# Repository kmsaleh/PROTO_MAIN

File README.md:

# PROTO_MAIN
This is my KICAD project files for the new PCB

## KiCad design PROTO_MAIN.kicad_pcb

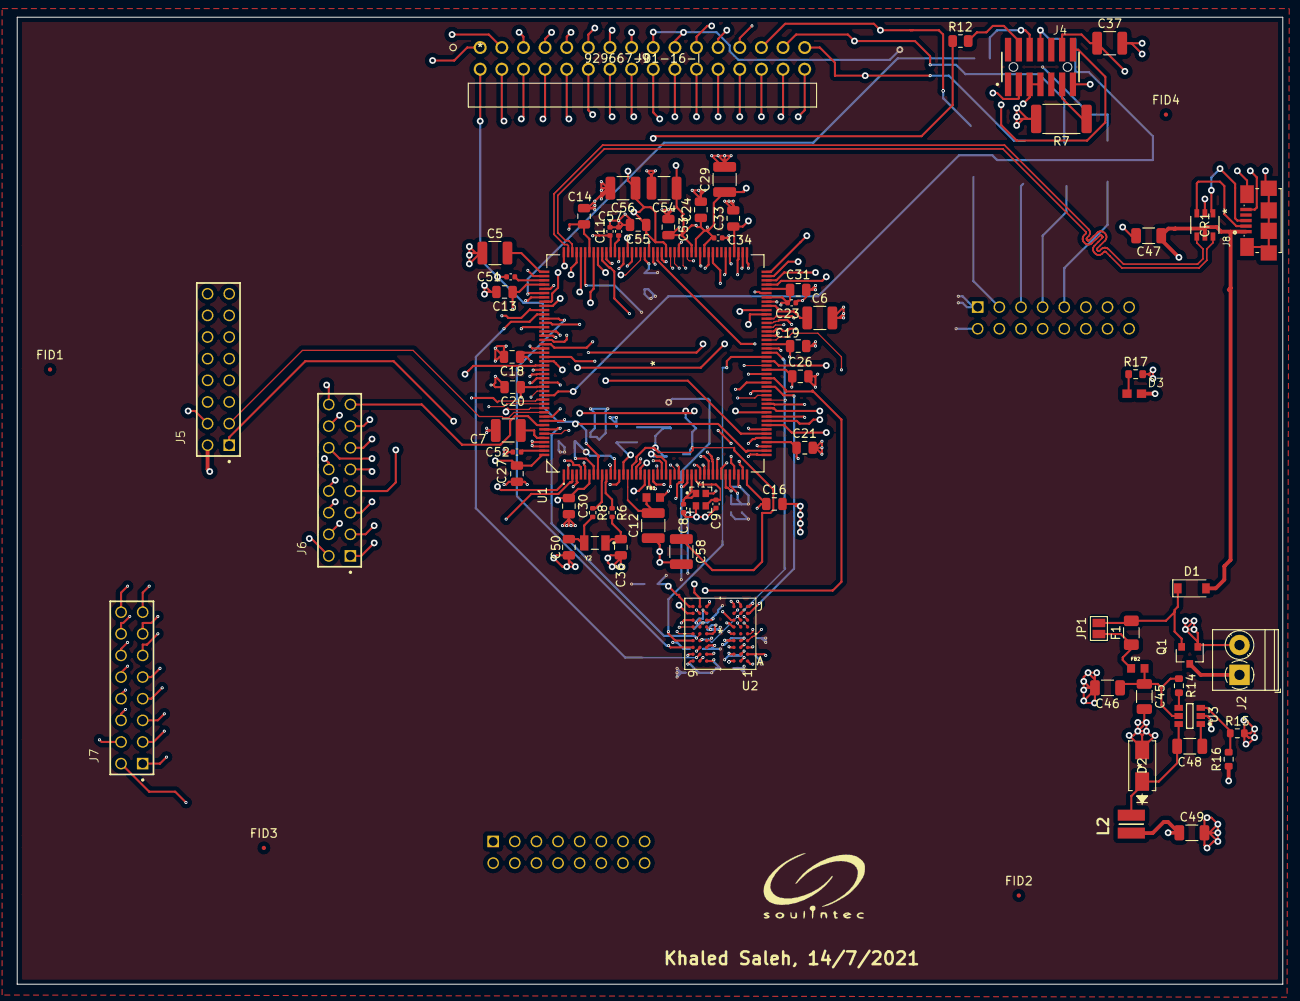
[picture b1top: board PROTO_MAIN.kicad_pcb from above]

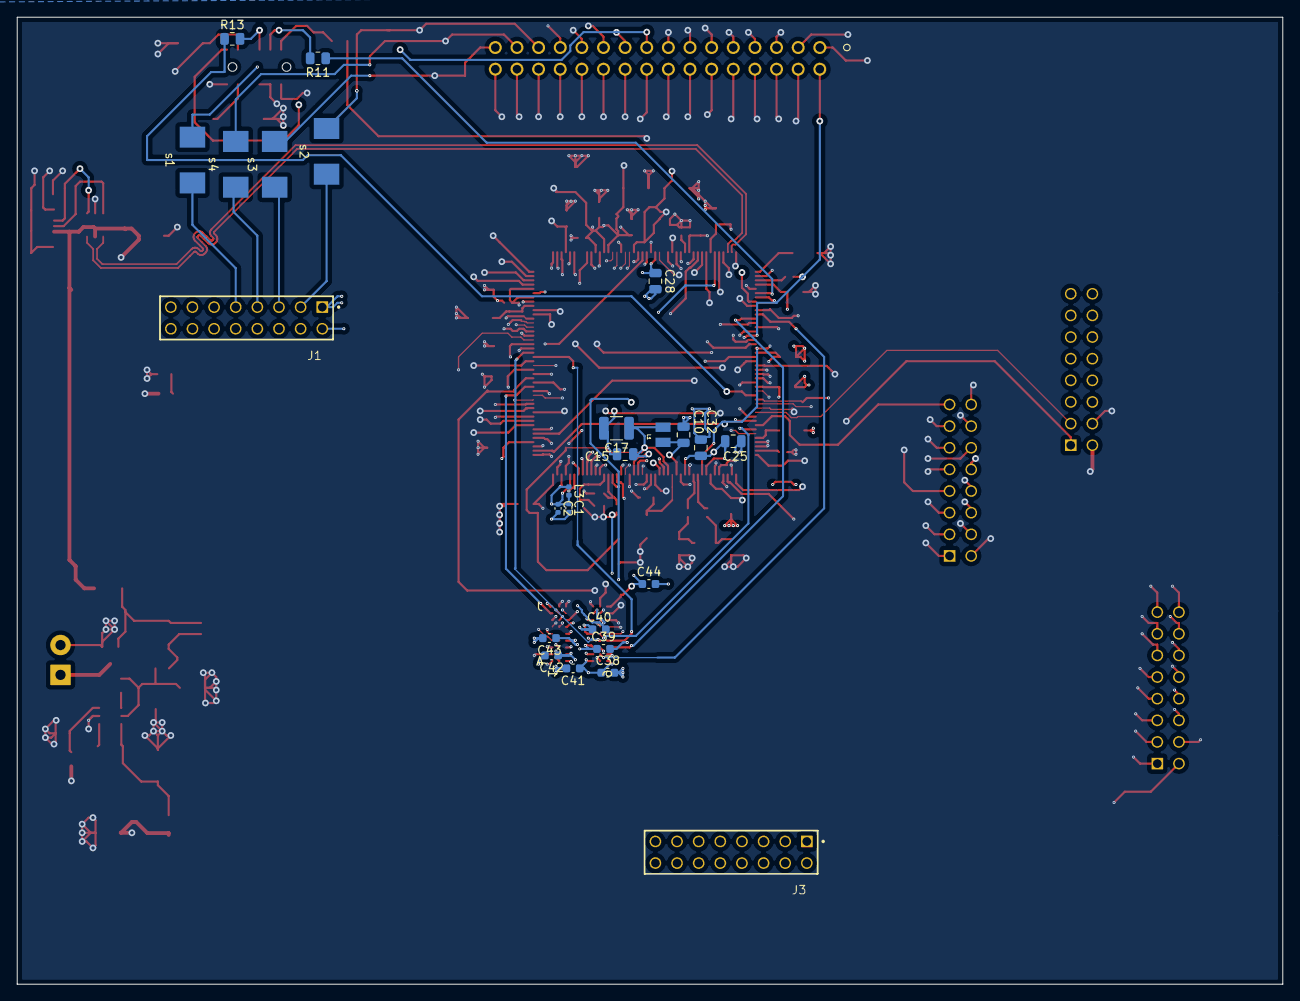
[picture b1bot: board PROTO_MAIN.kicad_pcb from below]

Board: 12 copper layers, 148.6 x 113.5 mm, 98 parts (25 on the bottom side), 144 nets.

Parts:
C1, C11, C57: 1uF; C_0402_1005Metric
C2: 10nF; C_0402_1005Metric
C5, C6, C7: 4.7uF; C_1210_3225Metric
C8, C9: 5.6pF; C_0402_1005Metric
C10: 220pF; C_0805_2012Metric
C12, C17, C58: 10uF; C_1210_3225Metric
C13, C14, C15, C16, C18, C19, C20, C21, C25, C26, C27, C28, C30, C31, C32, C33: 100uF; C_0805_2012Metric
C23, C34, C51, C52: 4.7uF; C_0402_1005Metric
C24, C53, C55: 100nF; C_0805_2012Metric
C29, C54, C56: 2.2uF; C_1210_3225Metric
C36, C50: 1.5pF; C_0805_2012Metric
C37: 0.1uF; C_1210_3225Metric
C38, C39, C40, C41, C42, C43, C44: 100nF; C_0603_1608Metric
C45: 10U; C_1206_3216Metric
C46: 10uF 25V; C_1206_3216Metric
C47: 100nF; C_1206_3216Metric
C48: 22nF; C_1206_3216Metric
C49: 22uF 6.3V; C_1206_3216Metric
CR1: USBLC6-4SC6
D1: B5819W; D_SOD-123
D2: B230A-13-F
D3: LED_Red; 0603
F1: 0685H9150-01; Fuse_1206_3216Metric
FB1, FB2: FBMJ1608HM180NTR; BEADC1608X100N
FID1, FID2, FID3, FID4: Fiducial; Fiducial_0.5mm_Mask1.5mm
J1, J3, J5, J6, J7: ZW-08-09-F-D-440-110; SAMTEC_ZW-08-09-F-D-440-110
J2: Screw_Terminal_01x02; TerminalBlock_Phoenix_PT-1,5-2-3.5-H_1x02_P3.50mm_Horizontal
J4: FTSH-107-01-L-DV-K-A; SAMTEC_FTSH-107-01-L-DV-K-A
J8: 10118192-0001LF; AMPHENOL_10118192-0001LF
J9: 929667-01-16-I
JP1: Jumper_NO_Small; SolderJumper-2_P1.3mm_Open_Pad1.0x1.5mm
L1: LQM2MPN2R2MG0L; INDC2016X100N
L2: 4.7uH; INDC3030X200N
L3: 39n; L_0402_1005Metric
Q1: AO3401A; SOT-23
R6, R8: 0R; R_0402_1005Metric
R7: 100R; R_2512_6332Metric
R11, R12, R13: 22R; R_0805_2012Metric
R14: 100K; R_0603_1608Metric
R15: 16.2K; R_0603_1608Metric
R16: 49.9k; R_0603_1608Metric
R17: 1k; R_0603_1608Metric
U1: STM32H747IIT6
U2: IS42S16160J-7BLI
U3: MP2359DT-LF-Z; Richtek_USA_Inc-RT8259GE-0
Y1: NX2016SA-25M-EXS00A-CS08742; OSCCC200X160X50N
Y2: NX3215SA-32.768K-STD-MUA-8; XTAL_NX3215SA-32.768K-STD-MUA-14
s1, s2, s3, s4: S1911-46R; S1621-46R

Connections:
+3V3: C1.1, C2.1, C11.1, C13.1, C14.1, C15.1, C16.1, C17.1, C18.1, C19.1, C20.1, C21.1, C23.1, C24.1, C25.1, C26.1, C27.1, C28.1, C29.1, C30.1, C31.1, C32.1, C33.1, C34.1, C38.1, C39.1, C41.1, C42.1, C43.1, C44.1, C49.1, C53.1, C54.1, C55.1, C56.1, D3.2, FB1.2, J1.02, J4.03, J5.04, L1.2, L2.2, L3.1, L3.2, R16.1, U1.7, U1.8, U1.13, U1.25, U1.39, U1.40, U1.44, U1.48, U1.65, U1.71, U1.82, U1.84, U1.92, U1.99, U1.101, U1.102, U1.108, U1.113, U1.121, U1.126, U1.136, U1.152, U1.160, U1.176, U2.A7, U2.A9, U2.B3, U2.C7, U2.D3, U2.J9
+5V: C47.1, CR1.5, D1.2, J5.02, J8.1
+12V: J2.1, Q1.3
/103: J9.32, U1.103
/104: J9.31, U1.104
/106: J9.30, U1.106
/107: J9.29, U1.107
/LCD_B0: J6.01, U1.158
/LCD_B1: J6.03, U1.156
/LCD_B2: J6.05, U1.154
/LCD_B3: J6.07, U1.155
/LCD_B4: J6.09, U1.129
/LCD_B5: J6.11, U1.46
/LCD_B6: J6.13, U1.168
/LCD_B7: J6.15, U1.169
/LCD_CLK: J6.14, U1.117
/LCD_DE: J6.08, U1.30
/LCD_DISP: J6.10, U1.1
/LCD_G0: J7.02, U1.56
/LCD_G1: J7.04, U1.5
/LCD_G2: J7.06, U1.51
/LCD_G3: J7.08, U1.125
/LCD_G4: J7.10, U1.78
/LCD_G5: J7.12, U1.79
/LCD_G6: J7.14, U1.123
/LCD_G7: J7.16, U1.118
/LCD_HSYNC: J6.02, U1.122
/LCD_INT: J6.06, U1.35
/LCD_R0: J7.01, U1.157
/LCD_R1: J7.03, U1.43
/LCD_R2: J7.05, U1.42
/LCD_R3: J7.07, U1.55
/LCD_R4: J7.09, U1.50
/LCD_R5: J7.11, U1.128
/LCD_R6: J7.13, U1.127
/LCD_R7: J7.15, U1.116
/LCD_RESET: J6.12, U1.2
/LCD_VSYNC: J6.04, U1.49
/NRST: C37.1, J4.12, U1.33
/PA0: J9.7, U1.41
/PA7: J9.8, U1.52
/PA15: J9.3, U1.139
/PB2: J9.11, U1.57
/PB4: J9.2, U1.163
/PB5: J9.1, U1.164
/PC0: J9.4, U1.34
/PC2_C: J9.5, U1.36
/PC3_C: J9.6, U1.37
/PC4: J9.9, U1.53
/PC5: J9.10, U1.54
/PC12: J9.23, U1.142
/PC13: J9.17, U1.9
/PD3: J9.24, U1.146
/PD4: J9.25, U1.147
/PD6: J9.26, U1.149
/PD7: J9.27, U1.150
/PE5: J9.18, U1.4
/PE7: J9.12, U1.67
/PF6: J9.19, U1.26
/PF7: J9.20, U1.27
/PF8: J9.21, U1.28
/PF9: J9.22, U1.29
/PG9: J9.28, U1.153
/RX: J4.13, U1.141
/SCL: J5.01, U1.165
/SDA: J5.03, U1.166
/SDRAM_A0: U1.18, U2.H7
/SDRAM_A1: U1.19, U2.H8
/SDRAM_A2: U1.20, U2.J8
/SDRAM_A3: U1.21, U2.J7
/SDRAM_A4: U1.22, U2.J3
/SDRAM_A5: U1.23, U2.J2
/SDRAM_A6: U1.59, U2.H3
/SDRAM_A7: U1.60, U2.H2
/SDRAM_A8: U1.61, U2.H1
/SDRAM_A9: U1.62, U2.G3
/SDRAM_A10: U1.63, U2.H9
/SDRAM_A11: U1.66, U2.G2
/SDRAM_A12: U1.110, U2.G1
/SDRAM_BA0: U1.111, U2.G7
/SDRAM_BA1: U1.114, U2.G8
/SDRAM_CLE: U1.94, U2.F3
/SDRAM_CLK: U1.145, U2.F2
/SDRAM_D0: U1.97, U2.A8
/SDRAM_D1: U1.98, U2.B9
/SDRAM_D2: U1.143, U2.B8
/SDRAM_D3: U1.144, U2.C9
/SDRAM_D4: U1.3, U2.C8
/SDRAM_D5: U1.68, U2.D9
/SDRAM_D6: U1.69, U2.D8
/SDRAM_D7: C40.1, U1.72, U2.E7, U2.E9
/SDRAM_D8: U1.73, U2.E1
/SDRAM_D9: U1.74, U2.D2
/SDRAM_D10: U1.75, U2.D1
/SDRAM_D11: U1.76, U2.C2
/SDRAM_D12: U1.77, U2.C1
/SDRAM_D13: U1.89, U2.B2
/SDRAM_D14: U1.90, U2.B1
/SDRAM_D15: U1.91, U2.A2
/SDRAM_NBL1: U1.171, U2.F1
/SDRAM_~CAS: U1.161, U1.170, U2.E8, U2.F7
/SDRAM_~CS: U1.124, U2.G9
/SDRAM_~RAS: U1.58, U2.F8
/SDRAM_~WE: U1.148, U2.F9
/SWCLK: R11.1, U1.138
/SWDIO: R12.1, U1.132
/SWO: R13.1, U1.162
/TX: J4.14, U1.140
BUCK_BST: C48.1, U3.1
BUCK_IN: C45.1, C46.1, FB2.2, R14.1, U3.5
GND: C1.2, C2.2, C5.2, C6.2, C7.2, C8.2, C9.2, C10.2, C11.2, C12.1, C13.2, C14.2, C15.2, C16.2, C17.2, C18.2, C19.2, C20.2, C21.2, C23.2, C24.2, C25.2, C26.2, C27.2, C28.2, C29.2, C30.2, C31.2, C32.2, C33.2, C34.2, C36.2, C37.2, C38.2, C39.2, C40.2, C41.2, C42.2, C43.2, C44.2, C45.2, C46.2, C47.2, C49.2, C50.2, C51.2, C52.2, C53.2, C54.2, C55.2, C56.2, C57.2, C58.2, CR1.2, D2.2, J1.01, J2.2, J4.05, J4.07, J6.16, J8.5, J8.SH1, J8.SH2, J8.SH3, J8.SH4, J8.SH5, J8.SH6, Q1.1, R7.2, R15.2, R17.2, U1.6, U1.12, U1.14, U1.24, U1.38, U1.45, U1.47, U1.64, U1.70, U1.81, U1.83, U1.93, U1.100, U1.105, U1.109, U1.112, U1.119, U1.134, U1.137, U1.151, U1.159, U1.167, U1.173, U1.174, U2.A1, U2.A3, U2.B7, U2.C3, U2.D7, U2.E3, U2.J1, U3.2, Y1.2, Y1.4
HSE_IN: C8.1, U1.31, Y1.1
HSE_OUT: C9.1, U1.32, Y1.3
unnamed: C5.1, U1.133
unnamed: C6.1, U1.80
unnamed: C7.1, U1.172
unnamed: C10.1, L1.1, U1.15
unnamed: C12.2, FB1.1, U1.16
unnamed: C36.1, R6.2, Y2.1
unnamed: C48.2, D2.1, L2.1, U3.6
unnamed: C50.1, R8.2, Y2.2
unnamed: C51.1, U1.135
unnamed: C52.1, U1.175
unnamed: C57.1, U1.120
unnamed: C58.1, U1.17
unnamed: D1.1, F1.2, JP1.1, Q1.2
unnamed: D3.1, R17.1
unnamed: F1.1, FB2.1, JP1.2
unnamed: J4.04, R12.2
unnamed: J4.06, R11.2
unnamed: J4.08, R13.2
unnamed: J4.11, R7.1
unnamed: R6.1, U1.11
unnamed: R8.1, U1.10
unnamed: R14.2, U3.4
unnamed: R15.1, R16.2, U3.3
PB12: J1.09, J9.13, U1.85, s1.1, s1.2
PB13: J1.03, J9.14, U1.86, s2.1, s2.2
PB14: J1.05, J9.16, U1.87, s3.1, s3.2
PB15: J1.07, J9.15, U1.88, s4.1, s4.2
USB_CONN_D+: CR1.1, J8.3
USB_CONN_D-: CR1.3, J8.2
USB_D+: CR1.4, U1.131
USB_D-: CR1.6, U1.130

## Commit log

2021-07-23 PROTO_MAIN_V01

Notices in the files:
parts and their libraries:
Copyright 2021 Accelerated Designs. All rights reserved.
Copyright 2016 Accelerated Designs. All rights reserved.
